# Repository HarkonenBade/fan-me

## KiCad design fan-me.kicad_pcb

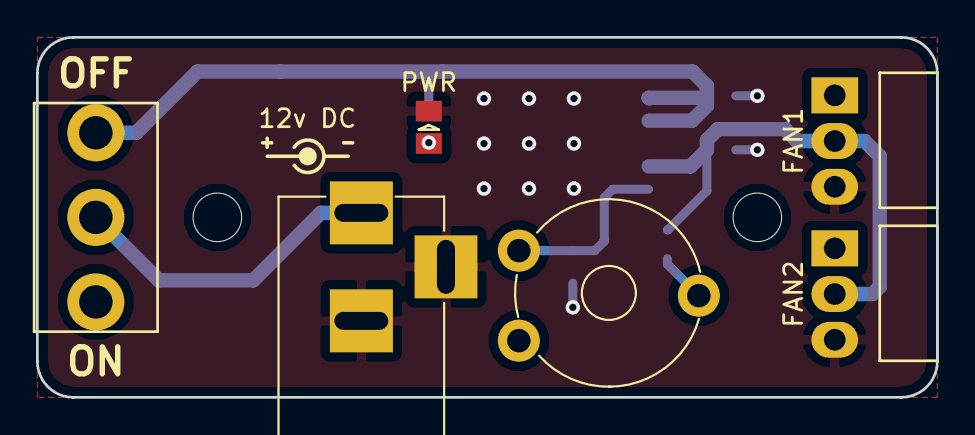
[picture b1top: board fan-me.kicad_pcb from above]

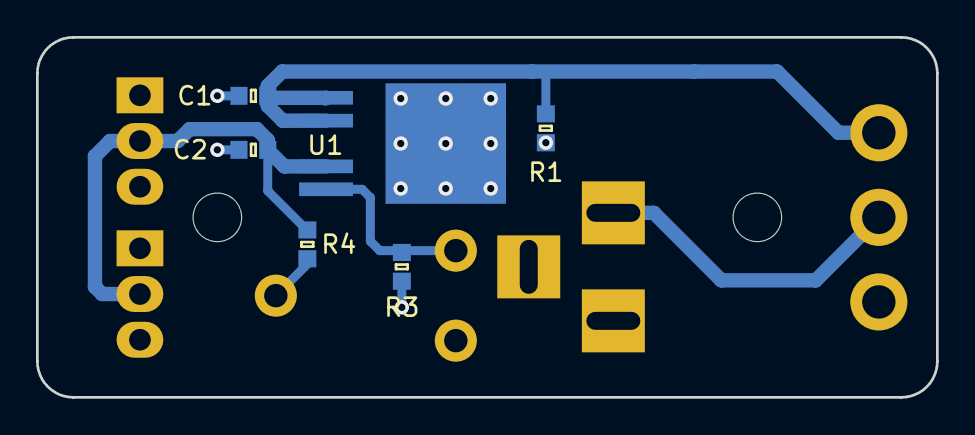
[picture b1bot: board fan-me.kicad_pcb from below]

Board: 2 copper layers, 50.0 x 20.0 mm, 14 parts (6 on the bottom side), 7 nets.

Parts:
C1: 1u; 0603
C2: 2u2; 0603
CON1: BARREL_JACK
D1: PWR; 0805-LED
J1: FAN1; Molex_KK-6410-03_03x2.54mm_Angle
J2: FAN2; Molex_KK-6410-03_03x2.54mm_Angle
R1: 1k; 0603
R3: 30k; 0603
R4: 200k; 0603
RV1: 220k; Potentiometer_Trimmer_Piher_PT-10v10_Horizontal_Px10.0mm_Py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
SW1: A1xxxxCxxx
U1: LDFPT-TR; PPAK
X1, X2: MountingHole_2.7mm_M2.5

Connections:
+12V: C1.1, R1.1, SW1.3, U1.1, U1.2
GND: C1.2, C2.2, CON1.2, CON1.3, D1.1, J1.3, J2.3, R3.2, U1.3
unnamed: C2.1, J1.2, J2.2, R4.1, U1.4
unnamed: CON1.1, SW1.2
unnamed: D1.2, R1.2
unnamed: R3.1, RV1.3, U1.5
unnamed: R4.2, RV1.2

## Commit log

2018-04-24 Initial
2018-04-26 More tweaking
2018-05-03 First pass board
2018-05-03 Tweaked first board version
2018-05-07 Mk2 board 30x50
2018-05-07 Board smollification mk3
2018-05-08 Add proper footprint for fan connectors
2018-05-16 Further tweaks ready for V1 boards
